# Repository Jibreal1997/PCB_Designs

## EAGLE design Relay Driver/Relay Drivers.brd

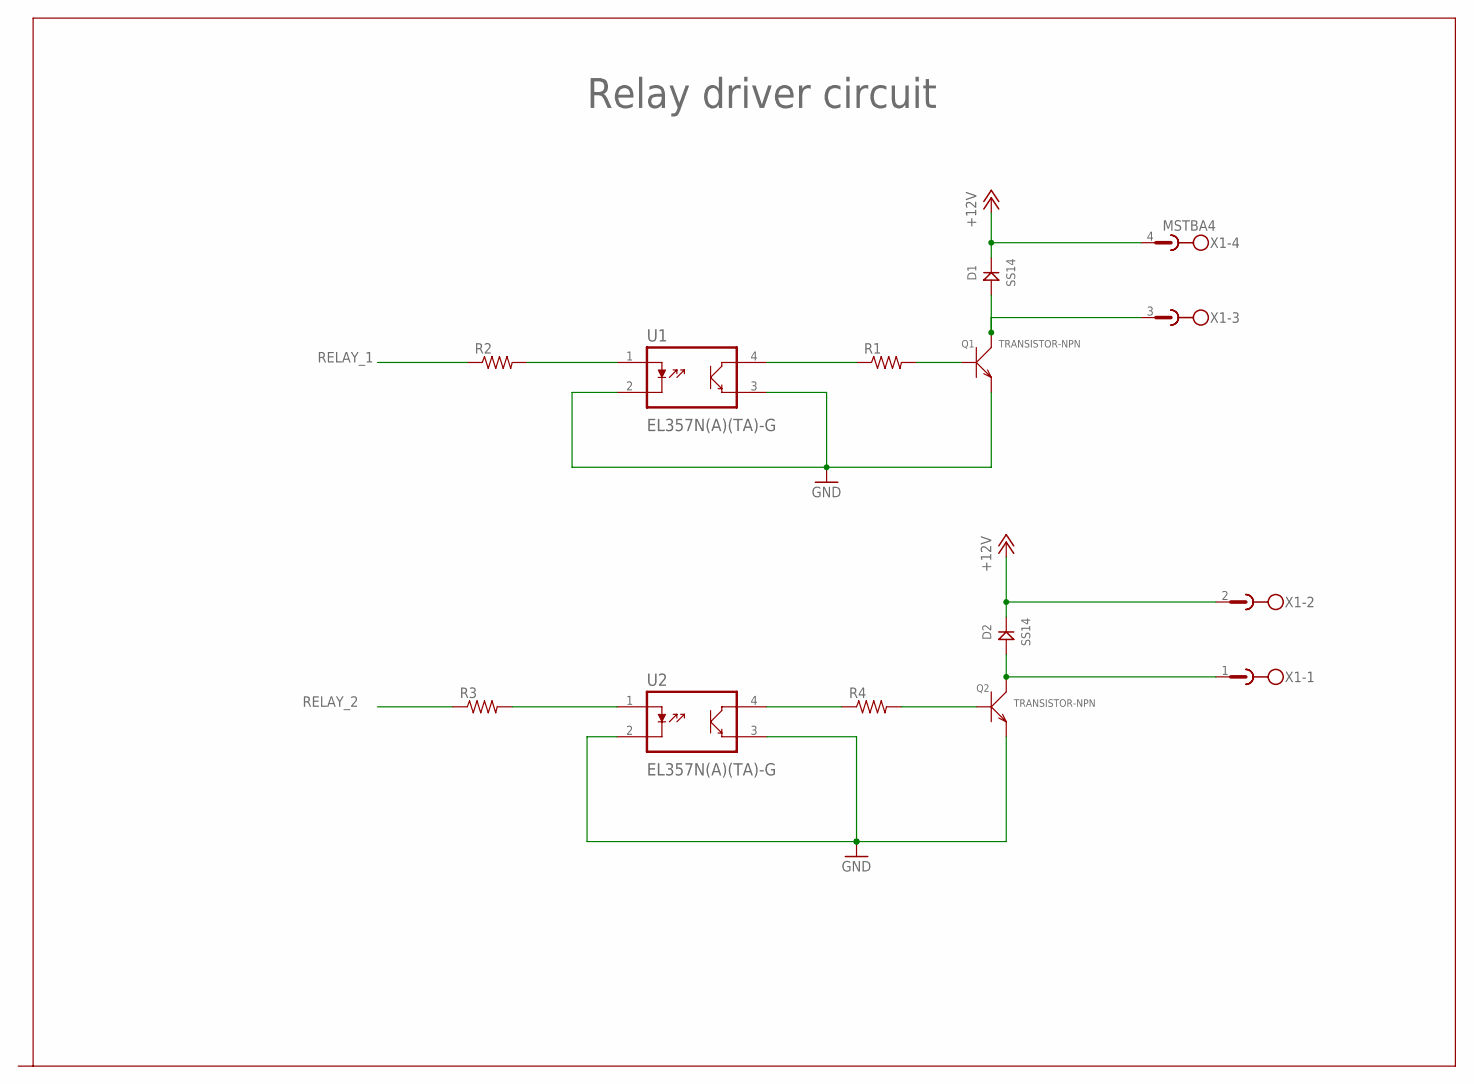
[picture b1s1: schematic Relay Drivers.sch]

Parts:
D1, D2: SS14; DO214
Q1, Q2: TRANSISTOR-NPN; SOT-23
R1, R2, R3, R4: R-US_R0805; R0805
U1, U2: EL357N(A)(TA)-G; SOP254P700X200-4N
X1: MSTBA4

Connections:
+12V: D1.CATHODE (KATHODE), D2.CATHODE (KATHODE), X1.2, X1.4
GND: Q1.2 (E), Q2.2 (E), U1.2 (K), U1.3 (E), U2.2 (K), U2.3 (E)
unnamed: R2.2, U1.1 (A)
unnamed: R1.1, U1.4 (C)
unnamed: Q1.1 (B), R1.2
unnamed: D1.ANODE, Q1.3 (C), X1.3
unnamed: R3.2, U2.1 (A)
unnamed: R4.1, U2.4 (C)
unnamed: Q2.1 (B), R4.2
unnamed: D2.ANODE, Q2.3 (C), X1.1
RELAY_1: R2.1
RELAY_2: R3.1

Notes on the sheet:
Relay driver circuit

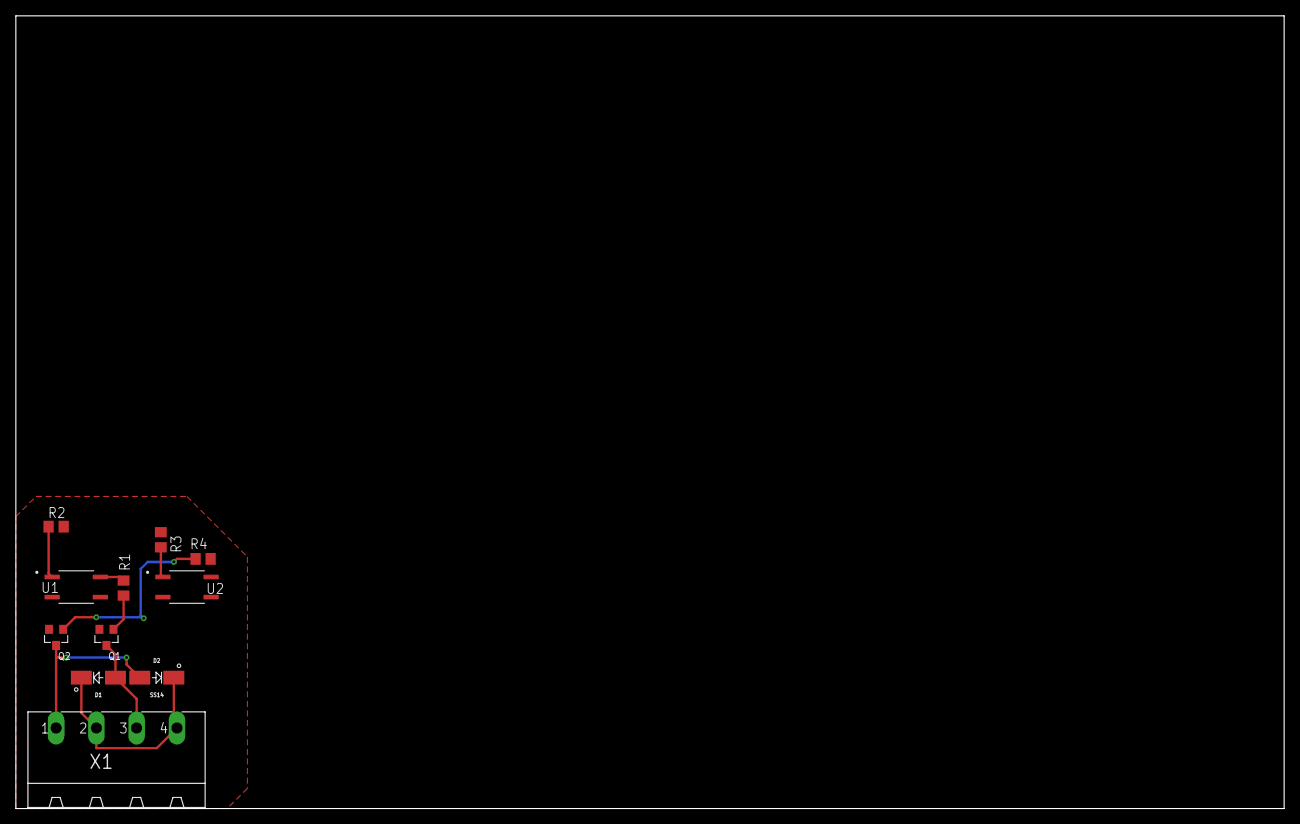
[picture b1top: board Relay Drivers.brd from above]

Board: 2 copper layers, 160.0 x 100.0 mm, 11 parts (0 on the bottom side), 10 nets.
